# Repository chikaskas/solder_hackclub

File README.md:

# solder_hackclub
**Submission** for https://solder.hackclub.com

**Description**: My PCB is very simple. There is a button that turns the LED on and a button that turns the LED off. I used a capacitor to store the charge provided by the battery through the push button and used 2 NPN transistors to amplify the current (so the capacitor doesn't discharge quickly).

**Bill**:
1x red LED, 
4x 4.7k resistor, 
2x NPN transistor, 
1x capacitor, 
2x push button, 
2x battery cell, 

**Pictures**:

Simulation:

Schematic:

PCB:

3D:

Made by @chikaskas

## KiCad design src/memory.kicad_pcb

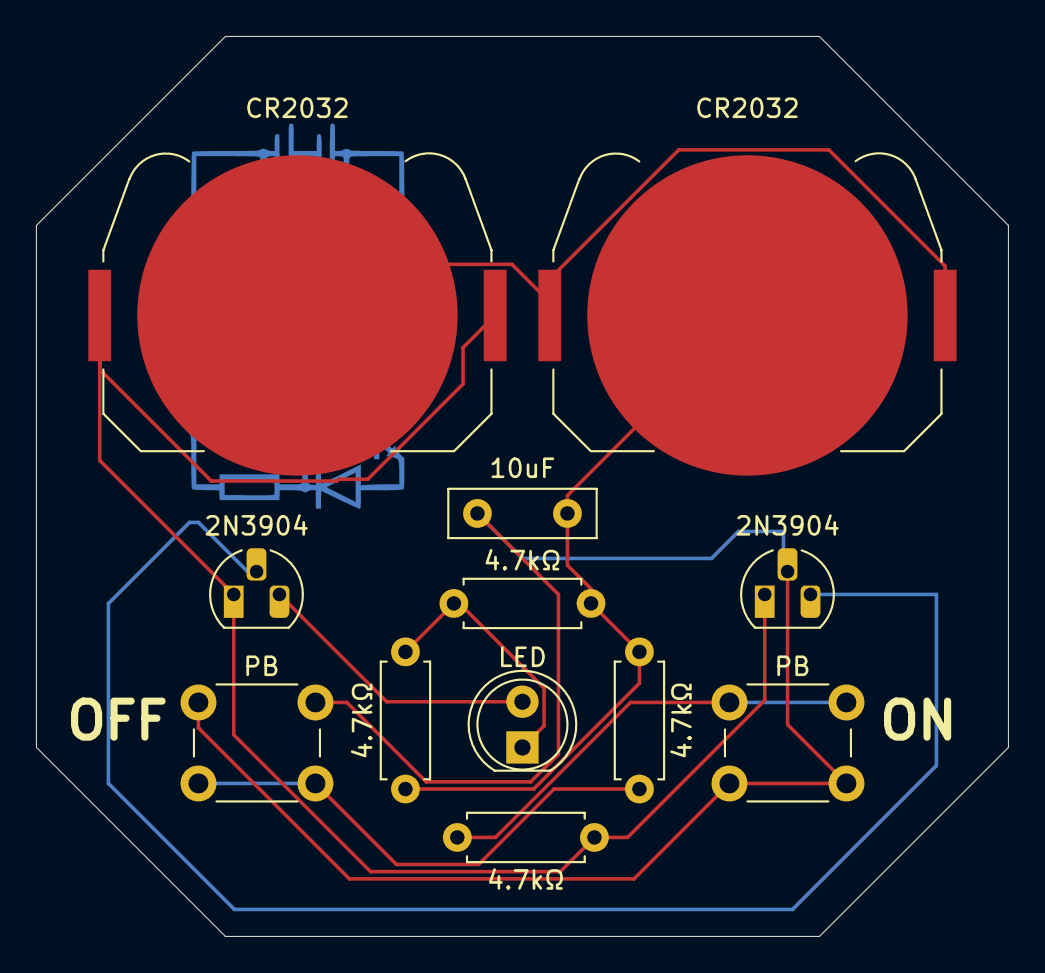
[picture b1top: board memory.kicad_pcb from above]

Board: 2 copper layers, 54.0 x 50.0 mm, 12 parts (0 on the bottom side), 8 nets.

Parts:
2N3904, 2N3904#2: NPN; TO-92L_HandSolder
4.7kΩ: R; R_Axial_DIN0207_L6.3mm_D2.5mm_P7.62mm_Horizontal
10uF: C; C_Disc_D8.0mm_W2.5mm_P5.00mm
BT1: Battery_Cell; BatteryHolder_Keystone_3034_1x20mm
CR2032: Battery_Cell; BatteryHolder_Keystone_3034_1x20mm
LED: LED; LED_D5.0mm
OFF: SW_Push; SW_PUSH_6mm
ON: SW_Push; SW_PUSH_6mm
R: 4.7kΩ; R_Axial_DIN0207_L6.3mm_D2.5mm_P7.62mm_Horizontal
R#2: 4.7kΩ; R_Axial_DIN0207_L6.3mm_D2.5mm_P7.62mm_Horizontal
R\: 4.7kΩ; R_Axial_DIN0207_L6.3mm_D2.5mm_P7.62mm_Horizontal

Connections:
unnamed: 2N3904.1 (C), 2N3904#2.1 (C), R\.2
unnamed: 4.7kΩ.2, 10uF.2, CR2032.2 (-), R.2, R#2.2
unnamed: 2N3904#2.3 (E), LED.2 (A)
unnamed: 4.7kΩ.1, LED.1 (K), R#2.1
unnamed: 2N3904.2 (B), 10uF.1, OFF.1, ON.2
unnamed: 2N3904.3 (E), 2N3904#2.2 (B)
unnamed: ON.1, R\.1
unnamed: OFF.2, R.1

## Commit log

2025-05-31 Add production folder and src folder
2025-05-31 Update README.md
    Fixed PCB screenshot.
2025-06-26 Update entire PCB
    README not updated
2025-06-29 Update back of PCB
